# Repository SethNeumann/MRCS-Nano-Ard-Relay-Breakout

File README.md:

# REPO NAME: MRCS-Nano-Ard-Relay-Breakout

## License: Creative Commons Attribution-NonCommercial-ShareAlike

A client wanted a simple automation controller to turn many sound animation units on and off
more less randomly.  He had the modules and gotten as far as turning them on and off with Arduino
relays. I discussed the project with contributor Jon Schmidt and created a sketch.  The board simply maps 
the Nanos D2-D3 and A0-A3 to male header pins with power and +5 in the appropriate places.  All you need to do 
make up cables with Dupont type cables (0.100 available for Pololu and many others) in the appropriate sizes.

Power is from a 5V wall wart which powers the Nano and associated relays

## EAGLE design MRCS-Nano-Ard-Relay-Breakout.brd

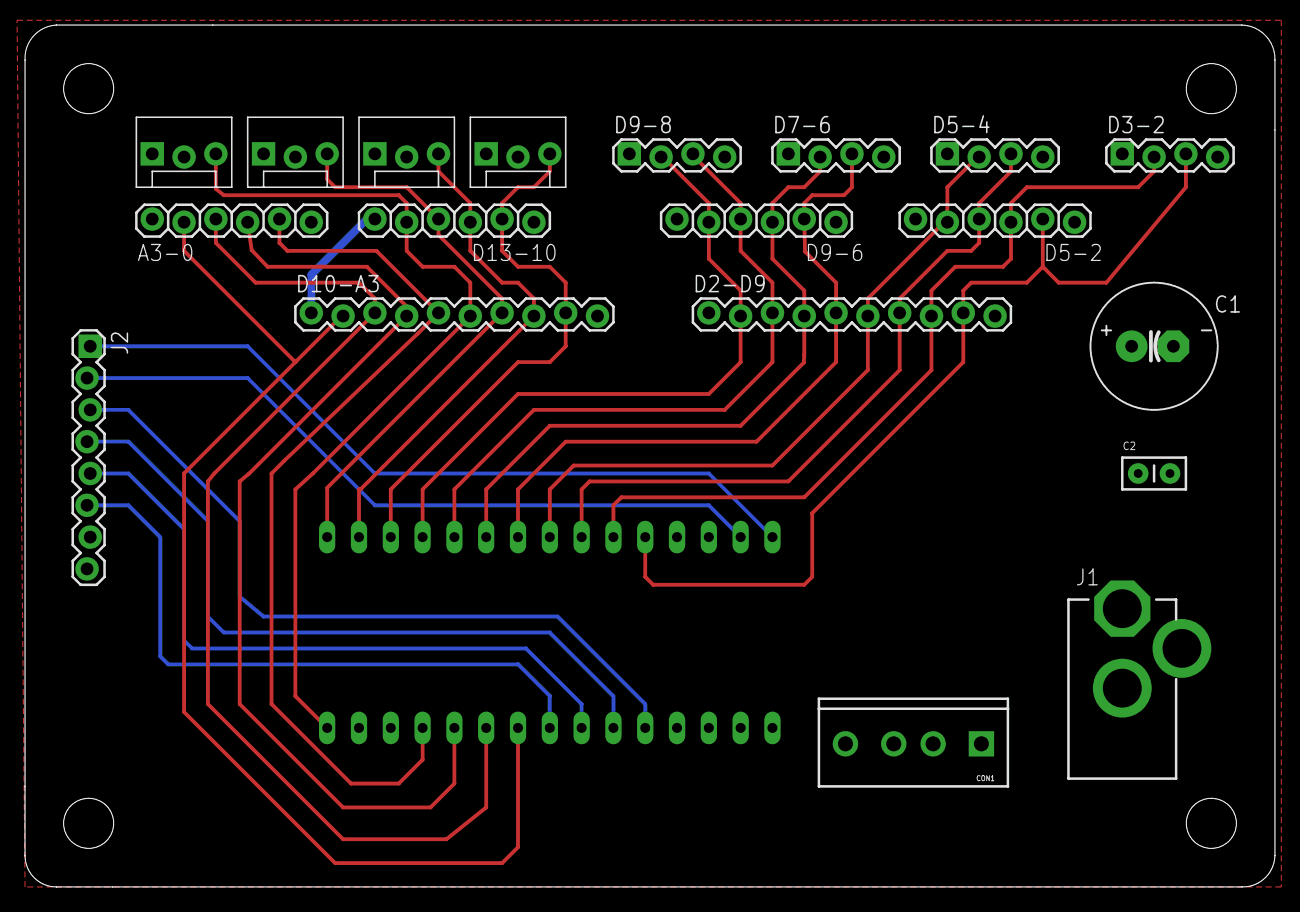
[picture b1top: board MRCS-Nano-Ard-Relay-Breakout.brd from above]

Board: 2 copper layers, 99.8 x 68.8 mm, 24 parts (0 on the bottom side), 24 nets.

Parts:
A3-0: 1X06_LOCK
C1: 470 uF @ 16V; E3.5-10
C2: .1 @ 25V; C-PTH-0.100
CON1: 5V PWR; SCREWTERMINAL-3.5MM-4_LOCK
D2-D9, D10-A3: CONNECTOR-M10LOCK; 1X10_LOCK
D3-2, D5-4, D7-6, D9-8: 1X04_LOCK
D5-2, D9-6, D13-10: 1X06_LOCK
D10, D11, D12, D13: CONNECTOR-M03MOLEX-254-LOCK; MOLEX-1X3_LOCK
J1: 5V PWR; DCJ0202
J2: Unused I/O; 1X08_LOCK
U$1: NANO
U$2: CA-PROP65WARNING
U$3: MRCSLOGOTOP
U$4: MRCSLOGOBTM
U$10: BOARD-DINRAIL-2.7IN

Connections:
5V: A3-0.1, C1.+, C2.1, CON1.2, CON1.4, D2-D9.1, D3-2.1, D5-2.1, D5-4.1, D7-6.1, D9-6.1, D9-8.1, D10.1, D10-A3.1, D11.1, D12.1, D13.1, D13-10.1, J1.1, J2.8, U$1.5V
A4: J2.6, U$1.A4
A5: J2.5, U$1.A5
A6: J2.4, U$1.A6
A7: J2.3, U$1.A7
GND: A3-0.6, C1.-, C2.2, CON1.1, CON1.3, D2-D9.10, D3-2.4, D5-2.6, D5-4.4, D7-6.4, D9-6.6, D9-8.4, D10.2, D10-A3.10, D11.2, D12.2, D13.2, D13-10.6, J1.2, J1.3, J2.7, U$1.GND, U$1.GND1
unnamed: D2-D9.9, D3-2.3, D5-2.5, U$1.D2
unnamed: D2-D9.8, D3-2.2, D5-2.4, U$1.D3
unnamed: D2-D9.5, D7-6.3, D9-6.5, U$1.D6
unnamed: D2-D9.4, D7-6.2, D9-6.4, U$1.D7
unnamed: D2-D9.3, D9-6.3, D9-8.3, U$1.D8
unnamed: D2-D9.2, D9-6.2, D9-8.2, U$1.D9
unnamed: D10.3, D10-A3.9, D13-10.5, U$1.D10
unnamed: D10-A3.8, D11.3, D13-10.4, U$1.D11
unnamed: D10-A3.7, D12.3, D13-10.3, U$1.D12
unnamed: D10-A3.6, D13.3, D13-10.2, U$1.D13
unnamed: A3-0.5, D10-A3.5, U$1.A0
unnamed: A3-0.4, D10-A3.4, U$1.A1
unnamed: A3-0.3, D10-A3.3, U$1.A2
unnamed: A3-0.2, D10-A3.2, U$1.A3
unnamed: D2-D9.7, D5-2.3, D5-4.3, U$1.D4
unnamed: D2-D9.6, D5-2.2, D5-4.2, U$1.D5
RX1: J2.2, U$1.RX1
TX0: J2.1, U$1.TX0

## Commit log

2022-03-15 initialcommit
2022-03-15 intial commit
2022-03-15 intiial commit
2022-03-15 setting up repository
    copied in a version of the Nano-Grade-Xing controller to start
2022-03-15 minor label changes after design review
2022-03-19 files as sent to jlcpcb for 1st run
    completion of design
2022-03-30 reflects first board
2022-05-07 fixed connectors 8 and 16 position Arduino Relays
    accidently selected 2mm rather than 2.54mm (0.100) connectors. Fixed positions of the singlets (different pattern of course).
2022-07-05 work files
2022-09-18 clean up of old files
    remove old files
2022-09-18 Create MRCS-Nano-Ard-Relay-Breakout BOM.pdf
    Bill of Materials
